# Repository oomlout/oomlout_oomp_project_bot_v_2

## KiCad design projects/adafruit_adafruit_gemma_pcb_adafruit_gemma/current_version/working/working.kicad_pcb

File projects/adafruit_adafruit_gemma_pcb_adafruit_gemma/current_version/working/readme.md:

# adafruit_gemma_pcb
 
## summary 
* id: adafruit_adafruit_gemma_pcb_adafruit_gemma
* user: adafruit
* name: adafruit_gemma_pcb
* board: adafruit_gemma
* repo: https://github.com/adafruit/Adafruit-Gemma-PCB

* src_file_repo_sch: 
* src_file_repo_sch_link: https://github.com/adafruit/Adafruit-Gemma-PCB/tree/master/
* full details link: https://github.com/oomlout/oomlout_oomp_project_bot_v_2/tree/main/projects/adafruit_adafruit_gemma_pcb_adafruit_gemma/current_version/working  

## schematic  
  
[schematic (pdf)](working_schematic.pdf) 

## pcb  

[board (pdf)](working.pdf)  

## working_bom
| Id | Designator | Footprint | Quantity | Designation | Supplier and ref |  | None | 
| --- | --- | --- | --- | --- | --- | --- | --- | 
| 1 | PWR0 | CHIPLED_0805_NOOUTLINE | 1 | green |  |  | [''] | 
| 2 | IC2 | SOT23-5L | 1 | MIC5225-3.3v |  |  | [''] | 
| 3 | C1,C8 | 0805-NO | 2 | 10uF |  |  | [''] | 
| 4 | X2 | 4UCONN_20329 | 1 | MicroUSB |  |  | [''] | 
| 5 | U$2 | ADAFRUIT_2.5MM | 1 |  |  |  | [''] | 
| 6 | VBAT0,B0,B1,B2,GND0,UNK3V3 | SEWINGTAP_2.0 | 6 | SEWTAP-2.0IN |  |  | [''] | 
| 7 | CN1 | JSTPH2 | 1 | JST-PH |  |  | [''] | 
| 8 | U1 | MLF20_4X4MM_0.5MM_ATMEL | 1 | ATTINY85 |  |  | [''] | 
| 9 | SW1 | EG1390 | 1 |  |  |  | [''] | 
| 10 | D2,D3 | SOD-123FL | 2 | SCHOTTKY |  |  | [''] | 
| 11 | R1,R2 | 0603-NO | 2 | 68 (0603) |  |  | [''] | 
| 12 | BOOT0 | CHIPLED_0805_NOOUTLINE | 1 | red |  |  | [''] | 
| 13 | R3 | 0603-NO | 1 | 1.5K (0603) |  |  | [''] | 
| 14 | Q1 | BTN_KMR2_4.6X2.8 | 1 | reset |  |  | [''] | 
| 15 | U$1,U$6 | FIDUCIAL_1MM | 2 | FIDUCIAL" |  |  | [''] | 
| 16 | R4,R5 | 0603-NO | 2 | 470 (0603) |  |  | [''] | 
| 17 | U$8 | SYMBOL_FCC_5MM | 1 |  |  |  | [''] | 
| 18 | U$10 | PCBFEAT-REV-040 | 1 |  |  |  | [''] | 
| 19 | U$7 | ADAFRUIT_5MM | 1 |  |  |  | [''] | 
| 20 | U$9 | SYMBOL_CE_5MM | 1 |  |  |  | [''] | 
| 21 | TP1 | B2,54 | 1 | TPB2,54 |  |  | [''] | 

## bom_schematic
| Ref | Qnty | Value | Cmp name | Footprint | Description | Vendor | DNP | 
| --- | --- | --- | --- | --- | --- | --- | --- | 
| B0, B1, B2 | 3 | SEWTAP-2.0IN | SEWTAP-2.0IN | working:SEWINGTAP_2.0 |  |  |  | 
| BOOT0 | 1 | red | LED0805_NOOUTLINE | working:CHIPLED_0805_NOOUTLINE |  |  |  | 
| C1, C8 | 2 | 10uF | CAP_CERAMIC0805-NOOUTLINE | working:0805-NO |  |  |  | 
| CN1 | 1 | JST-PH | CON_JST_PH_2PIN | working:JSTPH2 |  |  |  | 
| D2, D3 | 2 | SCHOTTKY | DIODE_SOD-123FL | working:SOD-123FL |  |  |  | 
| GND0 | 1 | SEWTAP-2.0IN | SEWTAP-2.0IN | working:SEWINGTAP_2.0 |  |  |  | 
| IC2 | 1 | LP298XS | LP298XS | working:SOT23-5L |  |  |  | 
| PWR0 | 1 | green | LED0805_NOOUTLINE | working:CHIPLED_0805_NOOUTLINE |  |  |  | 
| Q1 | 1 | reset | SWITCH_TACT_SMT4.6X2.8 | working:BTN_KMR2_4.6X2.8 |  |  |  | 
| R1, R2 | 2 | 68 (0603) | RESISTOR_0603_NOOUT | working:0603-NO |  |  |  | 
| R3 | 1 | 1.5K (0603) | RESISTOR_0603_NOOUT | working:0603-NO |  |  |  | 
| R4, R5 | 2 | 470 (0603) | RESISTOR_0603_NOOUT | working:0603-NO |  |  |  | 
| SW1 | 1 | SWITCH_DPDTEG1390 | SWITCH_DPDTEG1390 | working:EG1390 |  |  |  | 
| TP1 | 1 | TPB2,54 | TPB2,54 | working:B2,54 |  |  |  | 
| U1 | 1 | ATTINY85 | ATTINY85 | working:MLF20_4X4MM_0.5MM_ATMEL |  |  |  | 
| U$1, U$6 | 2 | FIDUCIAL"" | FIDUCIAL{dblquote}{dblquote} | working:FIDUCIAL_1MM |  |  |  | 
| UNK3V3 | 1 | SEWTAP-2.0IN | SEWTAP-2.0IN | working:SEWINGTAP_2.0 |  |  |  | 
| VBAT0 | 1 | SEWTAP-2.0IN | SEWTAP-2.0IN | working:SEWINGTAP_2.0 |  |  |  | 
| X2 | 1 | MicroUSB | USBMICRO_20329 | working:4UCONN_20329 |  |  |  |

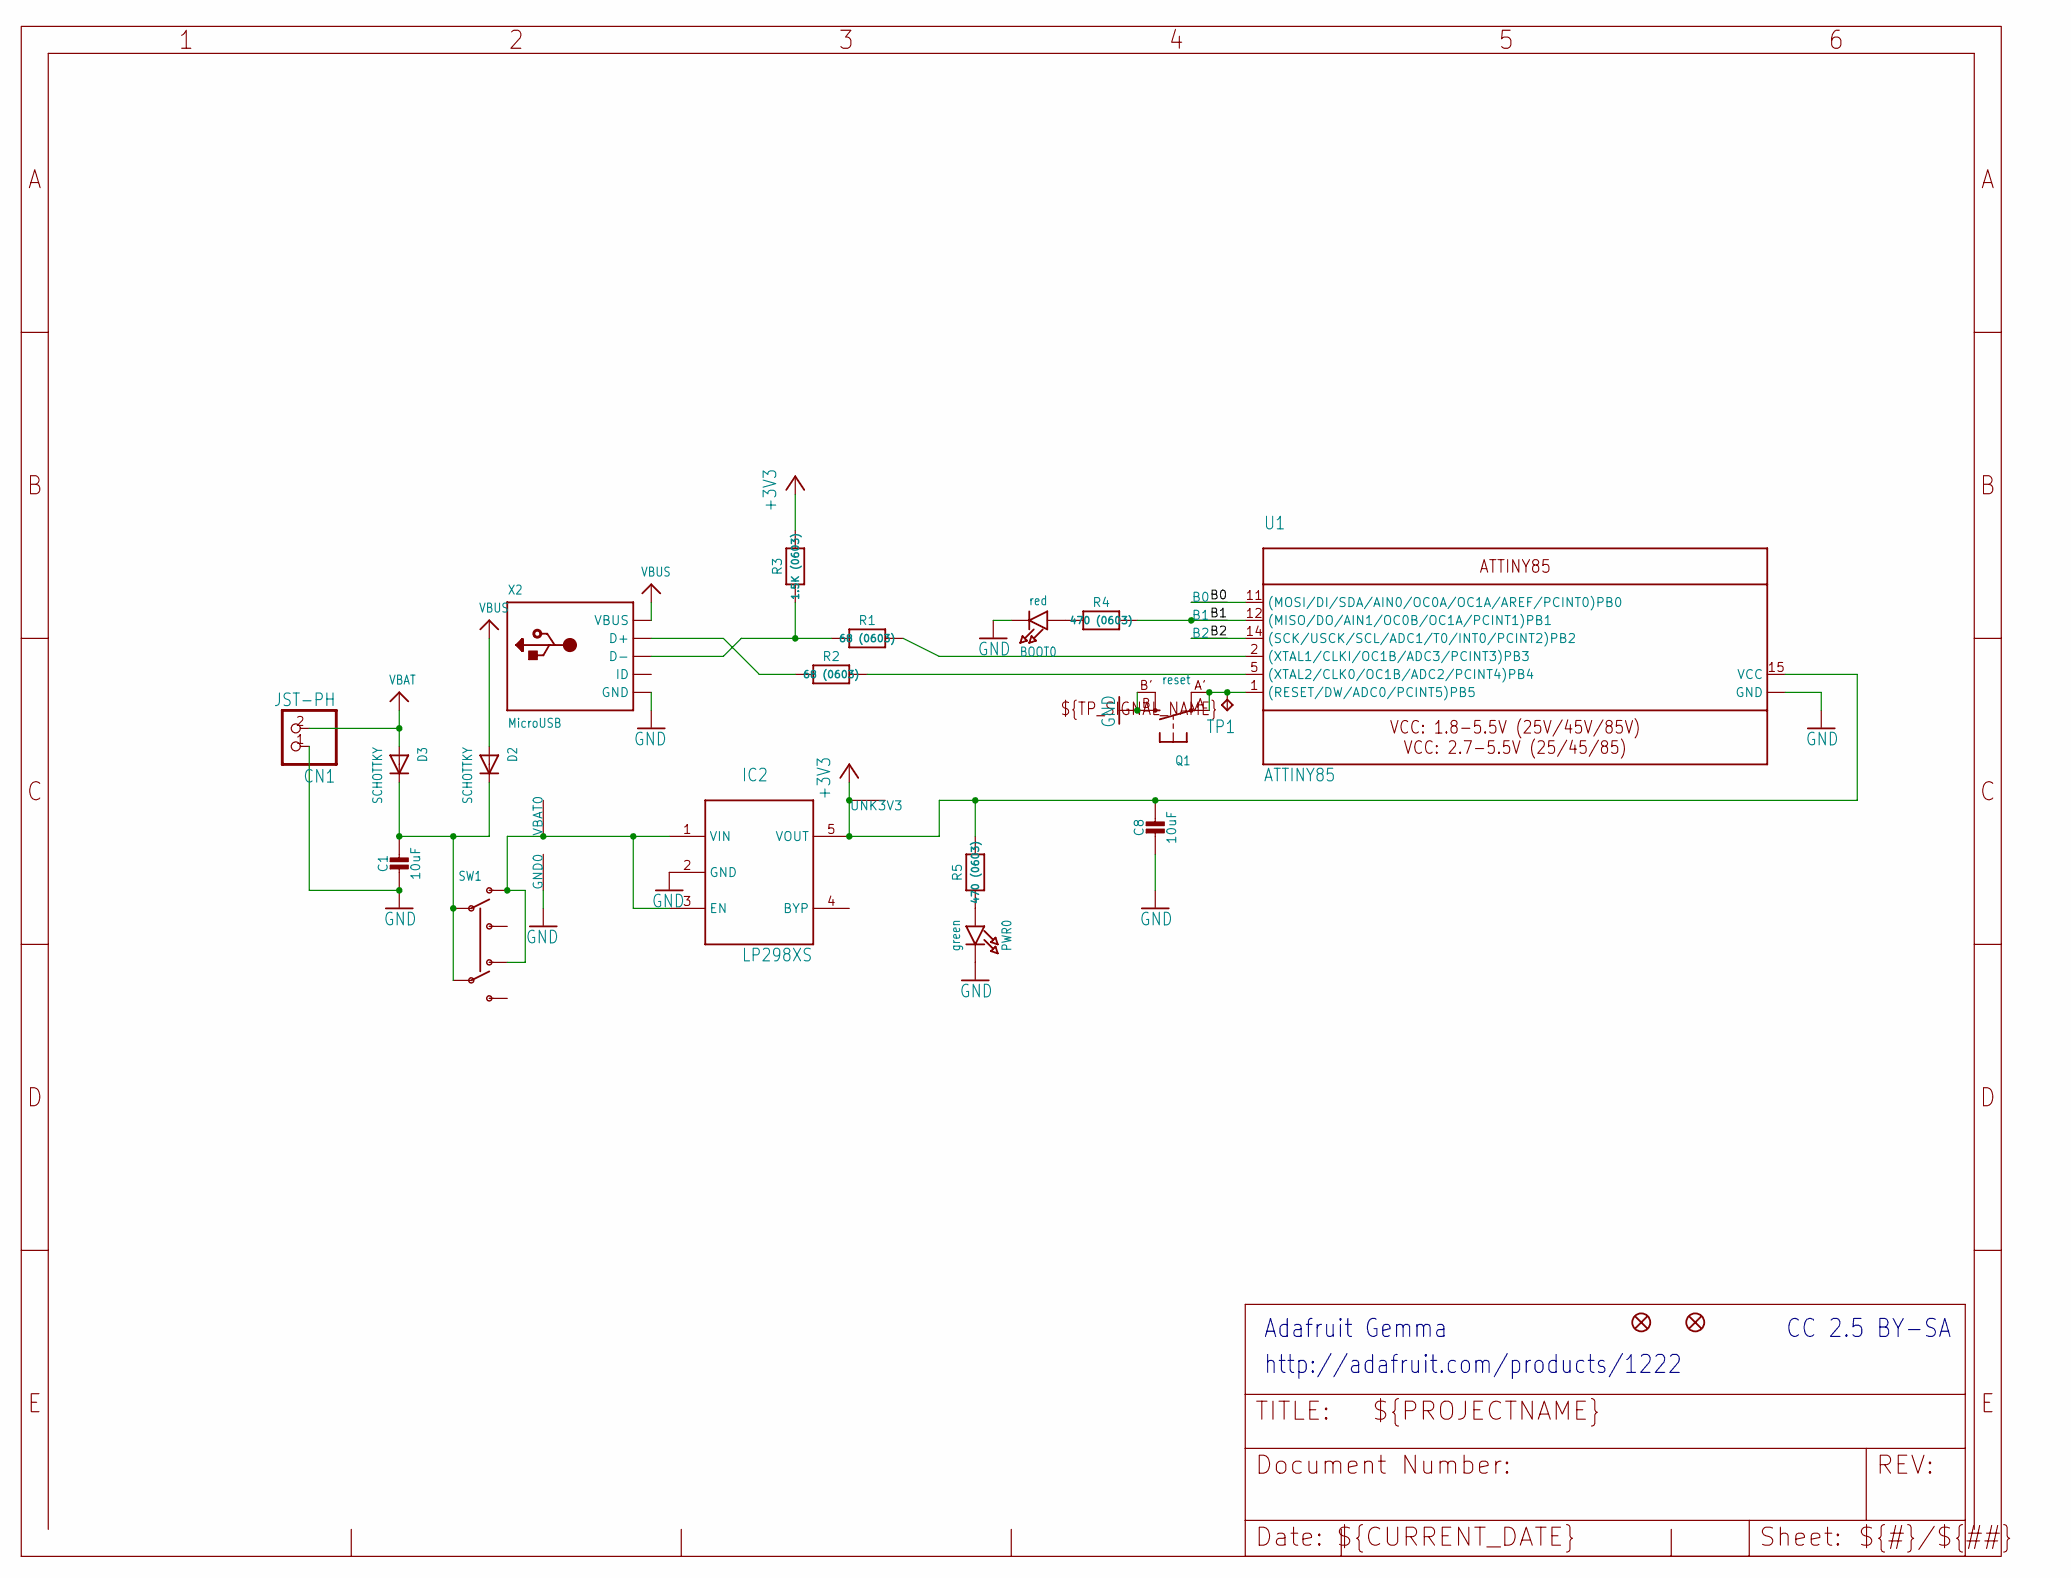
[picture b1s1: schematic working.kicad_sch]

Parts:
B0, B1, B2: SEWTAP-2.0IN; SEWINGTAP_2.0
BOOT0: red; CHIPLED_0805_NOOUTLINE
C1, C8: 10uF; 0805-NO
CN1: JST-PH; JSTPH2
D2, D3: SCHOTTKY; SOD-123FL
GND0: SEWTAP-2.0IN; SEWINGTAP_2.0
IC2: LP298XS; SOT23-5L
PWR0: green; CHIPLED_0805_NOOUTLINE
Q1: reset; BTN_KMR2_4.6X2.8
R1, R2: 68 (0603); 0603-NO
R3: 1.5K (0603); 0603-NO
R4, R5: 470 (0603); 0603-NO
SW1: SWITCH_DPDTEG1390; EG1390
TP1: TPB2,54; B2,54
U1: ATTINY85; MLF20_4X4MM_0.5MM_ATMEL
U$1, U$6: FIDUCIAL""; FIDUCIAL_1MM
UNK3V3: SEWTAP-2.0IN; SEWINGTAP_2.0
VBAT0: SEWTAP-2.0IN; SEWINGTAP_2.0
X2: MicroUSB; 4UCONN_20329

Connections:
+3V3: C8.1, IC2.5 (VOUT), R3.2, R5.2, U1.15 (VCC), UNK3V3.P$1
B0: B0.P$1, U1.11 ((MOSI/DI/SDA/AIN0/OC0A/OC1A/AREF/PCINT0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)
B1: B1.P$1, R4.2, U1.12 ((MISO/DO/AIN1/OC0B/OC1A/PCINT1)PB1)
B2: B2.P$1, U1.14 ((SCK/USCK/SCL/ADC1/T0/INT0/PCINT2)PB2)
GND: BOOT0.C, C1.2, C8.2, CN1.1, GND0.P$1, IC2.2 (GND), PWR0.C, Q1.B (S), Q1.B' (S1), U1.8 (GND), U1.THERMAL (GND), X2.BASE@1 (GND), X2.BASE@2 (GND), X2.GND, X2.SPRT@1 (GND), X2.SPRT@2 (GND), X2.SPRT@3 (GND), X2.SPRT@4 (GND)
unnamed: Q1.A, Q1.A' (P1), TP1.TP, U1.1 ((RESET/DW/ADC0/PCINT5)PB5)
unnamed: R2.1, X2.D+
unnamed: R1.2, U1.2 ((XTAL1/CLKI/OC1B/ADC3/PCINT3)PB3)
unnamed: R2.2, U1.5 ((XTAL2/CLK0/OC1B/ADC2/PCINT4)PB4)
unnamed: R1.1, R3.1, X2.D-
unnamed: BOOT0.A, R4.1
unnamed: IC2.1 (VIN), IC2.3 (EN), SW1.O1, SW1.O2, VBAT0.P$1
unnamed: PWR0.A, R5.1
unnamed: C1.1, D2.C, D3.C, SW1.P1, SW1.P2
VBAT: CN1.2, D3.A
VBUS: D2.A, X2.VBUS

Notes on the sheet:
Adafruit Gemma
http://adafruit.com/products/1222
CC 2.5 BY-SA

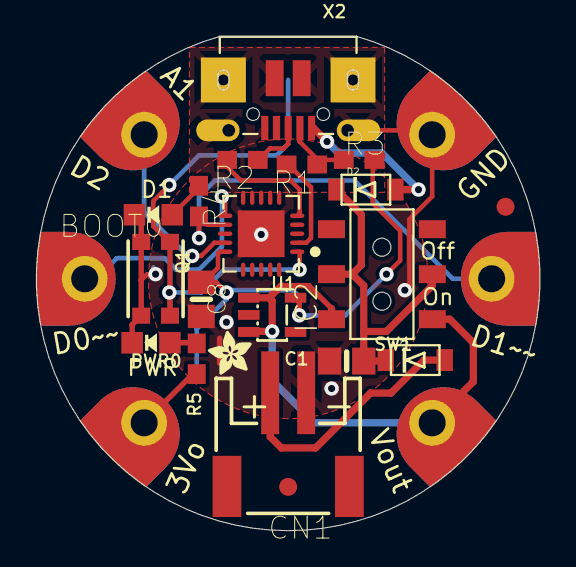
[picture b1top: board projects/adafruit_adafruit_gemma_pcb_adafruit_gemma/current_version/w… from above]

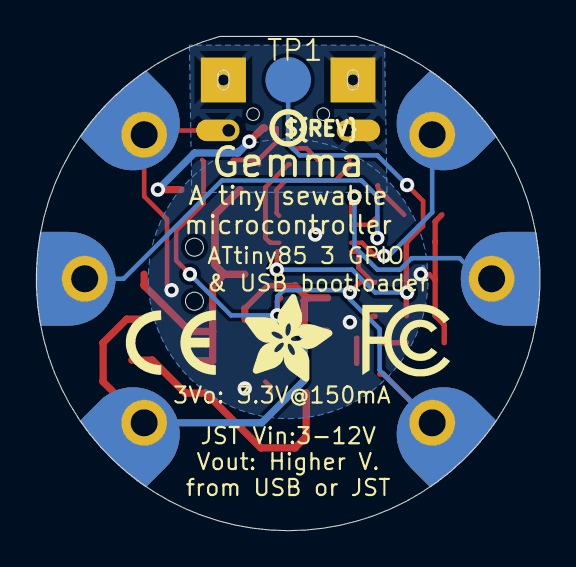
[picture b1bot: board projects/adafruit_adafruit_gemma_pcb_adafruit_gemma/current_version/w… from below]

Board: 16 copper layers, 28.0 x 27.5 mm, 31 parts (5 on the bottom side), 16 nets.

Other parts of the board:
U$2: ADAFRUIT_2.5MM
U$7: ADAFRUIT_5MM
U$8: SYMBOL_FCC_5MM
U$9: SYMBOL_CE_5MM
U$10: PCBFEAT-REV-040

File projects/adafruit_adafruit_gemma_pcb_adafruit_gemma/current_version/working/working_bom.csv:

"Id";"Designator";"Footprint";"Quantity";"Designation";"Supplier and ref";
1;"PWR0";"CHIPLED_0805_NOOUTLINE";1;"green";;;
2;"IC2";"SOT23-5L";1;"MIC5225-3.3v";;;
3;"C1,C8";"0805-NO";2;"10uF";;;
4;"X2";"4UCONN_20329";1;"MicroUSB";;;
5;"U$2";"ADAFRUIT_2.5MM";1;"";;;
6;"VBAT0,B0,B1,B2,GND0,UNK3V3";"SEWINGTAP_2.0";6;"SEWTAP-2.0IN";;;
7;"CN1";"JSTPH2";1;"JST-PH";;;
8;"U1";"MLF20_4X4MM_0.5MM_ATMEL";1;"ATTINY85";;;
9;"SW1";"EG1390";1;"";;;
10;"D2,D3";"SOD-123FL";2;"SCHOTTKY";;;
11;"R1,R2";"0603-NO";2;"68 (0603)";;;
12;"BOOT0";"CHIPLED_0805_NOOUTLINE";1;"red";;;
13;"R3";"0603-NO";1;"1.5K (0603)";;;
14;"Q1";"BTN_KMR2_4.6X2.8";1;"reset";;;
15;"U$1,U$6";"FIDUCIAL_1MM";2;"FIDUCIAL""";;;
16;"R4,R5";"0603-NO";2;"470 (0603)";;;
17;"U$8";"SYMBOL_FCC_5MM";1;"";;;
18;"U$10";"PCBFEAT-REV-040";1;"";;;
19;"U$7";"ADAFRUIT_5MM";1;"";;;
20;"U$9";"SYMBOL_CE_5MM";1;"";;;
21;"TP1";"B2,54";1;"TPB2,54";;;

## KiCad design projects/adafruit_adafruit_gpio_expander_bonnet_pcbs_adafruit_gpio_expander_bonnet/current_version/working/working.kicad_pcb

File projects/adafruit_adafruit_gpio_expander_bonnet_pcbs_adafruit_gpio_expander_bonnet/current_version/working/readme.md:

# adafruit_gpio_expander_bonnet_pcbs
 
## summary 
* id: adafruit_adafruit_gpio_expander_bonnet_pcbs_adafruit_gpio_expander_bonnet
* user: adafruit
* name: adafruit_gpio_expander_bonnet_pcbs
* board: adafruit_gpio_expander_bonnet
* repo: https://github.com/adafruit/Adafruit-GPIO-Expander-Bonnet-PCBs

* src_file_repo_sch: 
* src_file_repo_sch_link: https://github.com/adafruit/Adafruit-GPIO-Expander-Bonnet-PCBs/tree/master/
* full details link: https://github.com/oomlout/oomlout_oomp_project_bot_v_2/tree/main/projects/adafruit_adafruit_gpio_expander_bonnet_pcbs_adafruit_gpio_expander_bonnet/current_version/working  

## schematic  
  
[schematic (pdf)](working_schematic.pdf) 

## pcb  

[board (pdf)](working.pdf)  

## working_bom
| Id | Designator | Footprint | Quantity | Designation | Supplier and ref |  | None | 
| --- | --- | --- | --- | --- | --- | --- | --- | 
| 1 | IC1 | QFN28-ML_6X6MM | 1 | MCP23017ML |  |  | [''] | 
| 2 | U1 | SOT23-5 | 1 |  |  |  | [''] | 
| 3 | U$13 | PCBFEAT-REV-040 | 1 |  |  |  | [''] | 
| 4 | ADDR2,ADDR1,ADDR0 | SOLDERJUMPER_ARROW_NOPASTE | 3 |  |  |  | [''] | 
| 5 | R2,R3,R8,R9,R1,R4,R5,R6,R7 | 0603-NO | 9 | 10K |  |  | [''] | 
| 6 | Q2,Q1 | SOT23-WIDE | 2 | BSS138 |  |  | [''] | 
| 7 | FID1,FID2 | FIDUCIAL_1MM | 2 | FIDUCIAL_1MM |  |  | [''] | 
| 8 | JP8,JP3,JP5,JP6,JP9,JP1 | 1X02_ROUND | 6 |  |  |  | [''] | 
| 9 | RPI2 | PI_BONNET_2STEMMA_SMT | 1 | PIBONNET_STEMMA_2STEMMA_SMTTHM |  |  | [''] | 
| 10 | U$12 | ADAFRUIT_5MM | 1 |  |  |  | [''] | 
| 11 | JP2,JP7 | 2X08_SHROUDED | 2 |  |  |  | [''] | 
| 12 | C2 | 0603-NO | 1 | 0.1uF |  |  | [''] | 
| 13 | VIO_SELECT0 | SOLDERJUMPER_2WAY_OPEN_NOPASTE | 1 |  |  |  | [''] | 
| 14 | PIN1 | 1X21_ROUND_70MIL | 1 | HEADER-1X21 |  |  | [''] | 
| 15 | C3,C1 | 0805-NO | 2 | 10uF |  |  | [''] | 

## bom_schematic
| Ref | Qnty | Value | Cmp name | Footprint | Description | Vendor | DNP | 
| --- | --- | --- | --- | --- | --- | --- | --- | 
| ADDR0, ADDR1, ADDR2 | 3 | SOLDERJUMPER | SOLDERJUMPER | working:SOLDERJUMPER_ARROW_NOPASTE |  |  |  | 
| C1, C3 | 2 | 10uF | CAP_CERAMIC0805-NOOUTLINE | working:0805-NO |  |  |  | 
| C2 | 1 | 0.1uF | CAP_CERAMIC0603_NO | working:0603-NO |  |  |  | 
| FID1, FID2 | 2 | FIDUCIAL_1MM | FIDUCIAL_1MM | working:FIDUCIAL_1MM |  |  |  | 
| IC1 | 1 | MCP23017ML | MCP23017ML | working:QFN28-ML_6X6MM |  |  |  | 
| JP1, JP3, JP5, JP6, JP8, JP9 | 6 | HEADER-1X2ROUND | HEADER-1X2ROUND | working:1X02_ROUND |  |  |  | 
| JP2, JP7 | 2 | HEADER-2X8_SHROUDED | HEADER-2X8_SHROUDED | working:2X08_SHROUDED |  |  |  | 
| PIN1 | 1 | HEADER-1X21 | HEADER-1X21 | working:1X21_ROUND_70MIL |  |  |  | 
| Q1, Q2 | 2 | BSS138 | MOSFET-NWIDE | working:SOT23-WIDE |  |  |  | 
| R1, R2, R3, R4, R5, R6, R7, R8, R9 | 9 | 10K | RESISTOR_0603_NOOUT | working:0603-NO |  |  |  | 
| RPI2 | 1 | PIBONNET_STEMMA_2STEMMA_SMTTHM | PIBONNET_STEMMA_2STEMMA_SMTTHM | working:PI_BONNET_2STEMMA_SMT |  |  |  | 
| U1 | 1 | VREG_SOT23-5 | VREG_SOT23-5 | working:SOT23-5 |  |  |  | 
| VIO_SELECT0 | 1 | SOLDERJUMPER_2WAY | SOLDERJUMPER_2WAY | working:SOLDERJUMPER_2WAY_OPEN_NOPASTE |  |  |  |

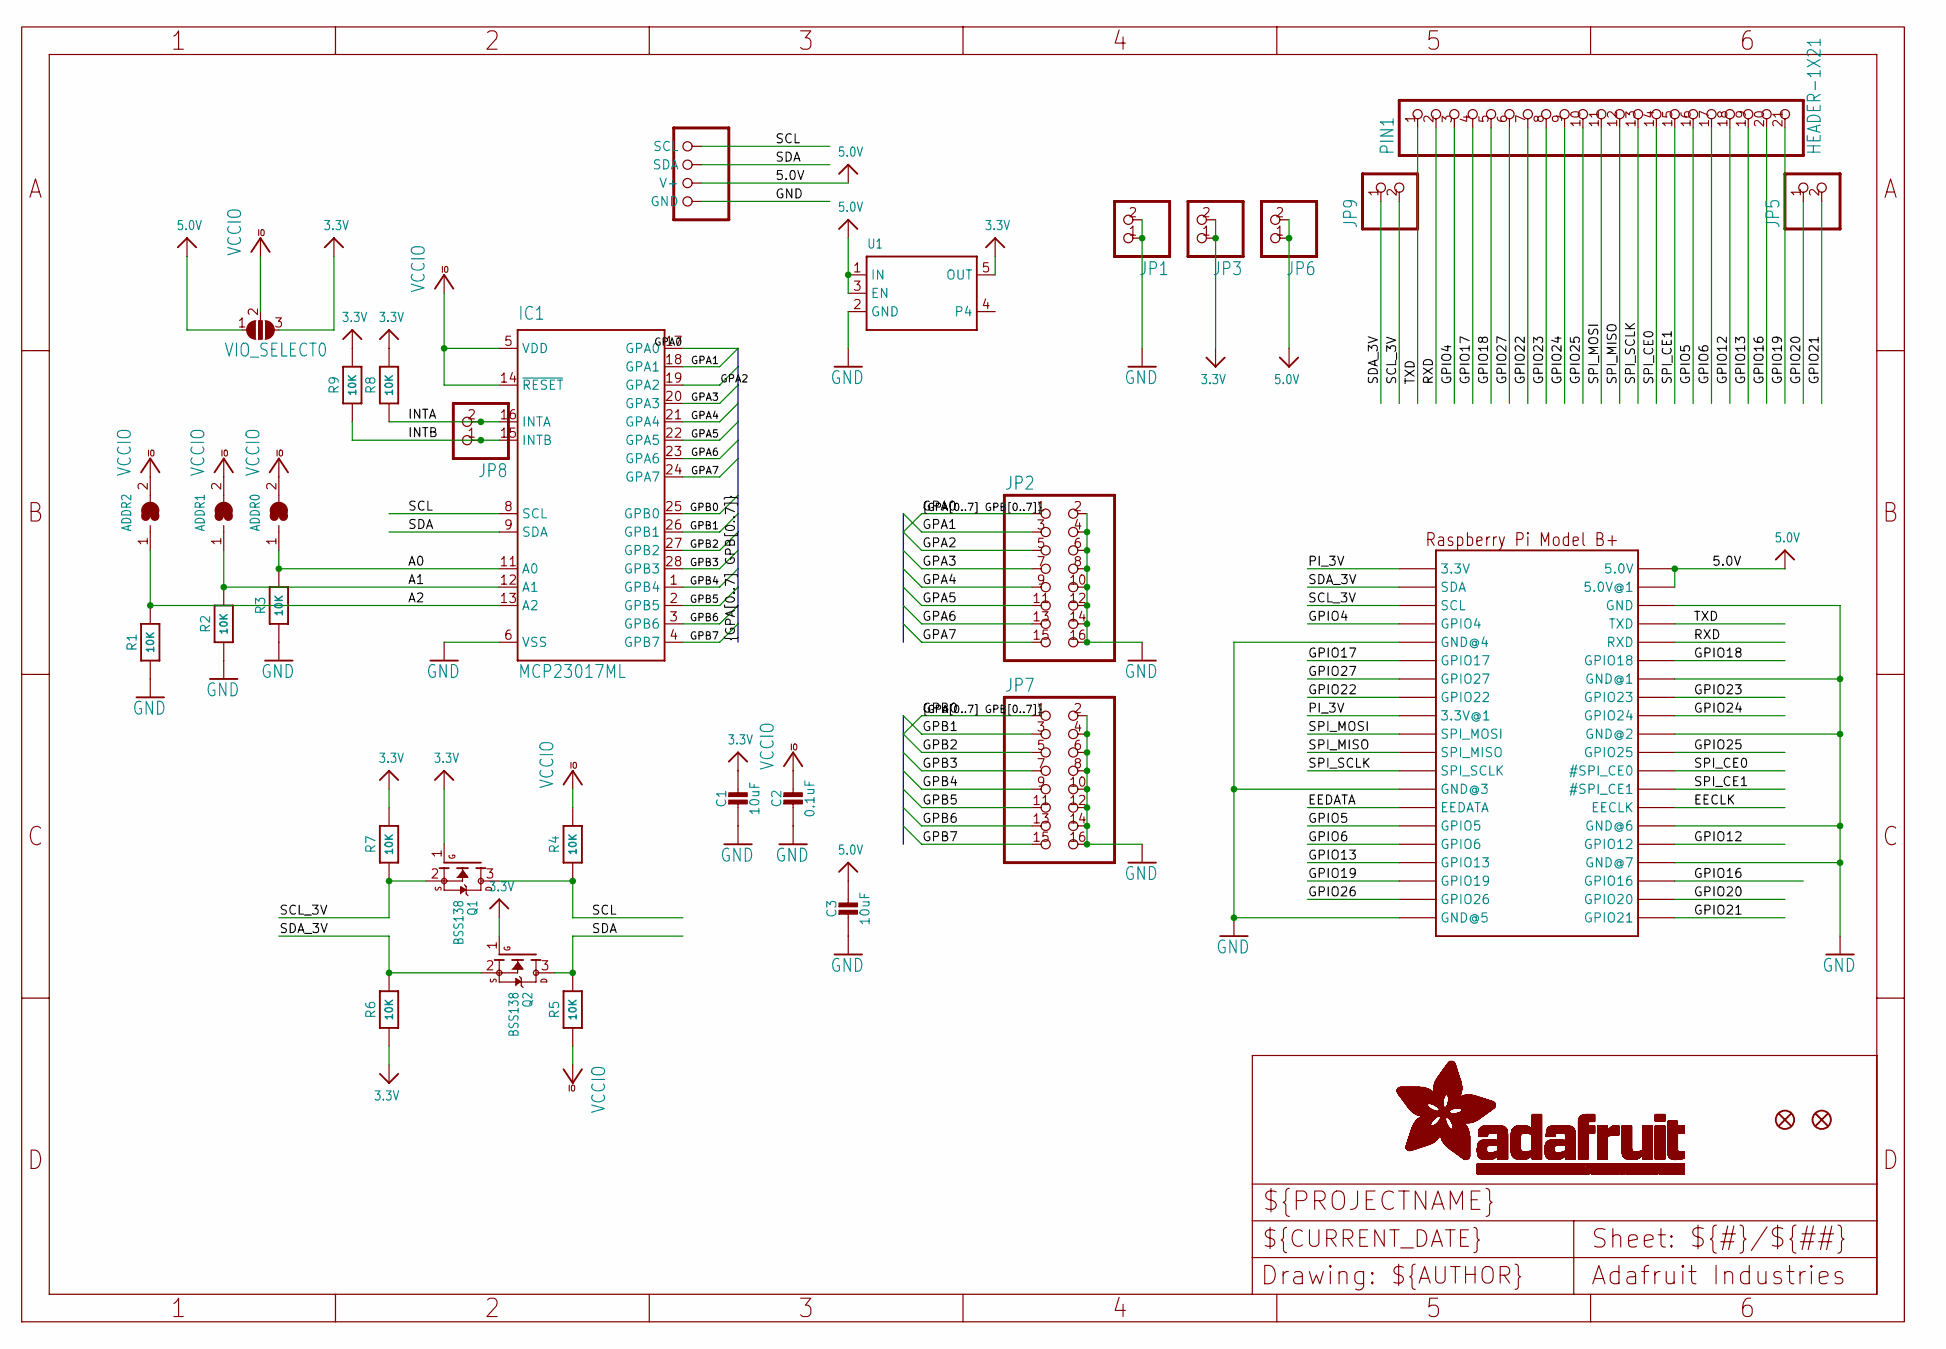
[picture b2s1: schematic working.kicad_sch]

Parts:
ADDR0, ADDR1, ADDR2: SOLDERJUMPER; SOLDERJUMPER_ARROW_NOPASTE
C1, C3: 10uF; 0805-NO
C2: 0.1uF; 0603-NO
FID1, FID2: FIDUCIAL_1MM
IC1: MCP23017ML; QFN28-ML_6X6MM
JP1, JP3, JP5, JP6, JP8, JP9: HEADER-1X2ROUND; 1X02_ROUND
JP2, JP7: HEADER-2X8_SHROUDED; 2X08_SHROUDED
PIN1: HEADER-1X21; 1X21_ROUND_70MIL
Q1, Q2: BSS138; SOT23-WIDE
R1, R2, R3, R4, R5, R6, R7, R8, R9: 10K; 0603-NO
RPI2: PIBONNET_STEMMA_2STEMMA_SMTTHM; PI_BONNET_2STEMMA_SMT
U1: VREG_SOT23-5; SOT23-5
VIO_SELECT0: SOLDERJUMPER_2WAY; SOLDERJUMPER_2WAY_OPEN_NOPASTE

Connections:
3.3V: C1.1, JP3.1, JP3.2, Q1.1 (G), Q2.1 (G), R6.1, R7.2, R8.2, R9.2, U1.5 (OUT), VIO_SELECT0.3
5.0V: C3.1, JP6.1, JP6.2, RPI2.2 (5.0V), RPI2.4 (5.0V@1), RPI2.S2 (5.0V), RPI2.S4 (5.0V@1), RPI2.V+, RPI2.V+1 (V+), U1.1 (IN), U1.3 (EN), VIO_SELECT0.1
A0: ADDR0.1, IC1.11 (A0), R3.2
A1: ADDR1.1, IC1.12 (A1), R2.2
A2: ADDR2.1, IC1.13 (A2), R1.2
EECLK: RPI2.28 (EECLK), RPI2.S28 (EECLK)
EEDATA: RPI2.27 (EEDATA), RPI2.S27 (EEDATA)
GND: C1.2, C2.2, C3.2, IC1.6 (VSS), JP1.1, JP1.2, JP2.2, JP2.4, JP2.6, JP2.8, JP2.10, JP2.12, JP2.14, JP2.16, JP7.2, JP7.4, JP7.6, JP7.8, JP7.10, JP7.12, JP7.14, JP7.16, R1.1, R2.1, R3.1, RPI2.6 (GND), RPI2.9 (GND@4), RPI2.14 (GND@1), RPI2.20 (GND@2), RPI2.25 (GND@3), RPI2.30 (GND@6), RPI2.34 (GND@7), RPI2.39 (GND@5), RPI2.GND, RPI2.GND1 (GND), RPI2.S6 (GND), RPI2.S9 (GND@4), RPI2.S14 (GND@1), RPI2.S20 (GND@2), RPI2.S25 (GND@3), RPI2.S30 (GND@6), RPI2.S34 (GND@7), RPI2.S39 (GND@5), U1.2 (GND)
GPA1: IC1.18 (GPA1), JP2.3
GPA2: IC1.19 (GPA2), JP2.5
GPA3: IC1.20 (GPA3), JP2.7
GPA4: IC1.21 (GPA4), JP2.9
GPA5: IC1.22 (GPA5), JP2.11
GPA6: IC1.23 (GPA6), JP2.13
GPA7: IC1.24 (GPA7), JP2.15
GPB1: IC1.26 (GPB1), JP7.3
GPB2: IC1.27 (GPB2), JP7.5
GPB3: IC1.28 (GPB3), JP7.7
GPB4: IC1.1 (GPB4), JP7.9
GPB5: IC1.2 (GPB5), JP7.11
GPB6: IC1.3 (GPB6), JP7.13
GPB7: IC1.4 (GPB7), JP7.15
GPIO4: PIN1.3, RPI2.7 (GPIO4), RPI2.S7 (GPIO4)
GPIO5: PIN1.16, RPI2.29 (GPIO5), RPI2.S29 (GPIO5)
GPIO6: PIN1.17, RPI2.31 (GPIO6), RPI2.S31 (GPIO6)
GPIO12: PIN1.18, RPI2.32 (GPIO12), RPI2.S32 (GPIO12)
GPIO13: PIN1.19, RPI2.33 (GPIO13), RPI2.S33 (GPIO13)
GPIO16: PIN1.20, RPI2.36 (GPIO16), RPI2.S36 (GPIO16)
GPIO17: PIN1.4, RPI2.11 (GPIO17), RPI2.S11 (GPIO17)
GPIO18: PIN1.5, RPI2.12 (GPIO18), RPI2.S12 (GPIO18)
GPIO19: PIN1.21, RPI2.35 (GPIO19), RPI2.S35 (GPIO19)
GPIO20: JP5.1, RPI2.38 (GPIO20), RPI2.S38 (GPIO20)
GPIO21: JP5.2, RPI2.40 (GPIO21), RPI2.S40 (GPIO21)
GPIO22: PIN1.7, RPI2.15 (GPIO22), RPI2.S15 (GPIO22)
GPIO23: PIN1.8, RPI2.16 (GPIO23), RPI2.S16 (GPIO23)
GPIO24: PIN1.9, RPI2.18 (GPIO24), RPI2.S18 (GPIO24)
GPIO25: PIN1.10, RPI2.22 (GPIO25), RPI2.S22 (GPIO25)
GPIO26: RPI2.37 (GPIO26), RPI2.S37 (GPIO26)
GPIO27: PIN1.6, RPI2.13 (GPIO27), RPI2.S13 (GPIO27)
INTA: IC1.16 (INTA), JP8.2, R8.1
INTB: IC1.15 (INTB), JP8.1, R9.1
PI_3V: RPI2.1 (3.3V), RPI2.17 (3.3V@1), RPI2.S1 (3.3V), RPI2.S17 (3.3V@1)
RXD: PIN1.2, RPI2.10 (RXD), RPI2.S10 (RXD)
SCL: IC1.8 (SCL), Q1.3 (D), R4.1, RPI2.SCL, RPI2.SCL1 (SCL)
SCL_3V: JP9.2, Q1.2 (S), R7.1, RPI2.5 (SCL), RPI2.S5 (SCL)
SDA: IC1.9 (SDA), Q2.3 (D), R5.2, RPI2.SDA, RPI2.SDA1 (SDA)
SDA_3V: JP9.1, Q2.2 (S), R6.2, RPI2.3 (SDA), RPI2.S3 (SDA)
SPI_CE0: PIN1.14, RPI2.24 (#SPI_CE0), RPI2.S24 (#SPI_CE0)
SPI_CE1: PIN1.15, RPI2.26 (#SPI_CE1), RPI2.S26 (#SPI_CE1)
SPI_MISO: PIN1.12, RPI2.21 (SPI_MISO), RPI2.S21 (SPI_MISO)
SPI_MOSI: PIN1.11, RPI2.19 (SPI_MOSI), RPI2.S19 (SPI_MOSI)
SPI_SCLK: PIN1.13, RPI2.23 (SPI_SCLK), RPI2.S23 (SPI_SCLK)
TXD: PIN1.1, RPI2.8 (TXD), RPI2.S8 (TXD)
VCCIO: ADDR0.2, ADDR1.2, ADDR2.2, C2.1, IC1.5 (VDD), IC1.14 (~RESET), R4.2, R5.1, VIO_SELECT0.2

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
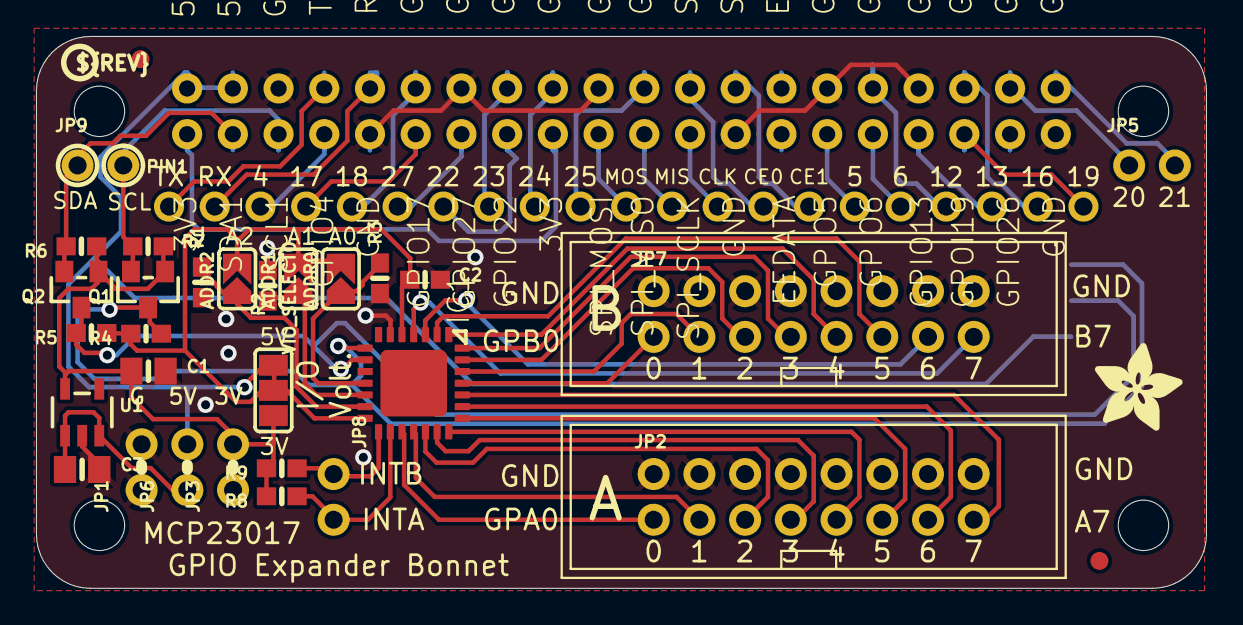
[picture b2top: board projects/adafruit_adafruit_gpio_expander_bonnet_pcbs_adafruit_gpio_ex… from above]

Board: 2 copper layers, 65.0 x 30.7 mm, 34 parts (0 on the bottom side), 56 nets.

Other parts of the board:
U$12: ADAFRUIT_5MM
U$13: PCBFEAT-REV-040

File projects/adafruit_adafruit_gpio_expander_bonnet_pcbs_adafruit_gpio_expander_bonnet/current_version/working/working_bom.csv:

"Id";"Designator";"Footprint";"Quantity";"Designation";"Supplier and ref";
1;"IC1";"QFN28-ML_6X6MM";1;"MCP23017ML";;;
2;"U1";"SOT23-5";1;"";;;
3;"U$13";"PCBFEAT-REV-040";1;"";;;
4;"ADDR2,ADDR1,ADDR0";"SOLDERJUMPER_ARROW_NOPASTE";3;"";;;
5;"R2,R3,R8,R9,R1,R4,R5,R6,R7";"0603-NO";9;"10K";;;
6;"Q2,Q1";"SOT23-WIDE";2;"BSS138";;;
7;"FID1,FID2";"FIDUCIAL_1MM";2;"FIDUCIAL_1MM";;;
8;"JP8,JP3,JP5,JP6,JP9,JP1";"1X02_ROUND";6;"";;;
9;"RPI2";"PI_BONNET_2STEMMA_SMT";1;"PIBONNET_STEMMA_2STEMMA_SMTTHM";;;
10;"U$12";"ADAFRUIT_5MM";1;"";;;
11;"JP2,JP7";"2X08_SHROUDED";2;"";;;
12;"C2";"0603-NO";1;"0.1uF";;;
13;"VIO_SELECT0";"SOLDERJUMPER_2WAY_OPEN_NOPASTE";1;"";;;
14;"PIN1";"1X21_ROUND_70MIL";1;"HEADER-1X21";;;
15;"C3,C1";"0805-NO";2;"10uF";;;

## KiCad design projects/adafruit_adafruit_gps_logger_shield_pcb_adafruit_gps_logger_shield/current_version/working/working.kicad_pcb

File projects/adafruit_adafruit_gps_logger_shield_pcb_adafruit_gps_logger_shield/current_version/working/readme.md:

# adafruit_gps_logger_shield_pcb
 
## summary 
* id: adafruit_adafruit_gps_logger_shield_pcb_adafruit_gps_logger_shield
* user: adafruit
* name: adafruit_gps_logger_shield_pcb
* board: adafruit_gps_logger_shield
* repo: https://github.com/adafruit/Adafruit-GPS-Logger-Shield-PCB

* src_file_repo_sch: 
* src_file_repo_sch_link: https://github.com/adafruit/Adafruit-GPS-Logger-Shield-PCB/tree/master/
* full details link: https://github.com/oomlout/oomlout_oomp_project_bot_v_2/tree/main/projects/adafruit_adafruit_gps_logger_shield_pcb_adafruit_gps_logger_shield/current_version/working  

## schematic  
  
[schematic (pdf)](working_schematic.pdf) 

## pcb  

[board (pdf)](working.pdf)  

## working_bom
| Id | Designator | Footprint | Quantity | Designation | Supplier and ref |  | None | 
| --- | --- | --- | --- | --- | --- | --- | --- | 
| 1 | FB1 | 0805@1 | 1 | Ferrite |  |  | [''] | 
| 2 | @HOLE0,@HOLE2,@HOLE1 |  | 3 |  |  |  | [''] | 
| 3 | C2,C3 | 0805@1 | 2 | 10uF |  |  | [''] | 
| 4 | U1 | FGPMMOPA6H | 1 | FGPMMOPA6H |  |  | [''] | 
| 5 | FID2,FID1 | FIDUCIAL_1MM | 2 | FIDUCIAL" |  |  | [''] | 
| 6 | JP9,JP6 | 1X06-BIG | 2 |  |  |  | [''] | 
| 7 | U$9 | 1X10-BIG | 1 | PINHD-1X10 |  |  | [''] | 
| 8 | RESET0 | EVQ-Q2 | 1 | Reset |  |  | [''] | 
| 9 | R9,R10 | 0805 | 2 | 1k |  |  | [''] | 
| 10 | U$13 | ADAFRUIT_5MM | 1 |  |  |  | [''] | 
| 11 | R5 | 0805 | 1 | 10K |  |  | [''] | 
| 12 | C1 | 0805@1 | 1 | 0.1uF |  |  | [''] | 
| 13 | LED5 | CHIPLED_0805 | 1 | green |  |  | [''] | 
| 14 | U4 | SOIC16 | 1 | 4050 |  |  | [''] | 
| 15 | U2 | SOT23-5 | 1 | MIC5225-3.3 |  |  | [''] | 
| 16 | JP4,JP1 | 1X08-BIG | 2 | D0-D7 |  |  | [''] | 
| 17 | R1 | 0805 | 1 | 1K |  |  | [''] | 
| 18 | B1 | CR1220 | 1 | CR1220 |  |  | [''] | 
| 19 | SW1 | EG1390 | 1 |  |  |  | [''] | 
| 20 | U$20 | U.FL | 1 | U.FL |  |  | [''] | 
| 21 | CN2 | MICROSD | 1 |  |  |  | [''] | 
| 22 | LED4 | CHIPLED_0805 | 1 | yellow |  |  | [''] | 
| 23 | U3 | ARDUINOR3 | 1 | ARDUINOR3-DIMENSION |  |  | [''] | 
| 24 | LED1 | CHIPLED_0805 | 1 | red |  |  | [''] | 
| 25 | U$15 | ADAFRUIT_TEXT_30MM | 1 |  |  |  | [''] | 

## bom_schematic
| Ref | Qnty | Value | Cmp name | Footprint | Description | Vendor | DNP | 
| --- | --- | --- | --- | --- | --- | --- | --- | 
| B1 | 1 | CR1220 | BATTERYCR1220_SMT | working:CR1220 |  |  |  | 
| C1 | 1 | 0.1uF | CAP_CERAMIC0805 | working:0805@1 |  |  |  | 
| C2, C3 | 2 | 10uF | CAP_CERAMIC0805 | working:0805@1 |  |  |  | 
| CN2 | 1 | MICROSD | MICROSD | working:MICROSD |  |  |  | 
| FB1 | 1 | Ferrite | FERRITE0805 | working:0805@1 |  |  |  | 
| FID1, FID2 | 2 | FIDUCIAL"" | FIDUCIAL{dblquote}{dblquote} | working:FIDUCIAL_1MM |  |  |  | 
| JP1, JP4 | 2 | D0-D7 | PINHD-1X8BIG | working:1X08-BIG |  |  |  | 
| JP6, JP9 | 2 | PINHD-1X6B | PINHD-1X6B | working:1X06-BIG |  |  |  | 
| LED1 | 1 | red | LED0805 | working:CHIPLED_0805 |  |  |  | 
| LED4 | 1 | yellow | LED0805 | working:CHIPLED_0805 |  |  |  | 
| LED5 | 1 | green | LED0805 | working:CHIPLED_0805 |  |  |  | 
| R1 | 1 | 1K | RESISTOR0805 | working:0805 |  |  |  | 
| R5 | 1 | 10K | RESISTOR0805 | working:0805 |  |  |  | 
| R9, R10 | 2 | 1k | RESISTOR0805 | working:0805 |  |  |  | 
| RESET0 | 1 | SPST_TACT-EVQQ2 | SPST_TACT-EVQQ2 | working:EVQ-Q2 |  |  |  | 
| SW1 | 1 | DPDT-EG1390 | DPDT-EG1390 | working:EG1390 |  |  |  | 
| U1 | 1 | FGPMMOPA6H | GPS_FGPMMOPA6H | working:FGPMMOPA6H |  |  |  | 
| U2 | 1 | MIC5225-3.3 | VREG_SOT23-5 | working:SOT23-5 |  |  |  | 
| U3 | 1 | ARDUINOR3-DIMENSION | ARDUINOR3-DIMENSION | working:ARDUINOR3 |  |  |  | 
| U4 | 1 | 4050 | 74HC4050D | working:SOIC16 |  |  |  | 
| U$9 | 1 | PINHD-1X10 | PINHD-1X10 | working:1X10-BIG |  |  |  | 
| U$20 | 1 | U.FL | U.FL | working:U.FL |  |  |  |

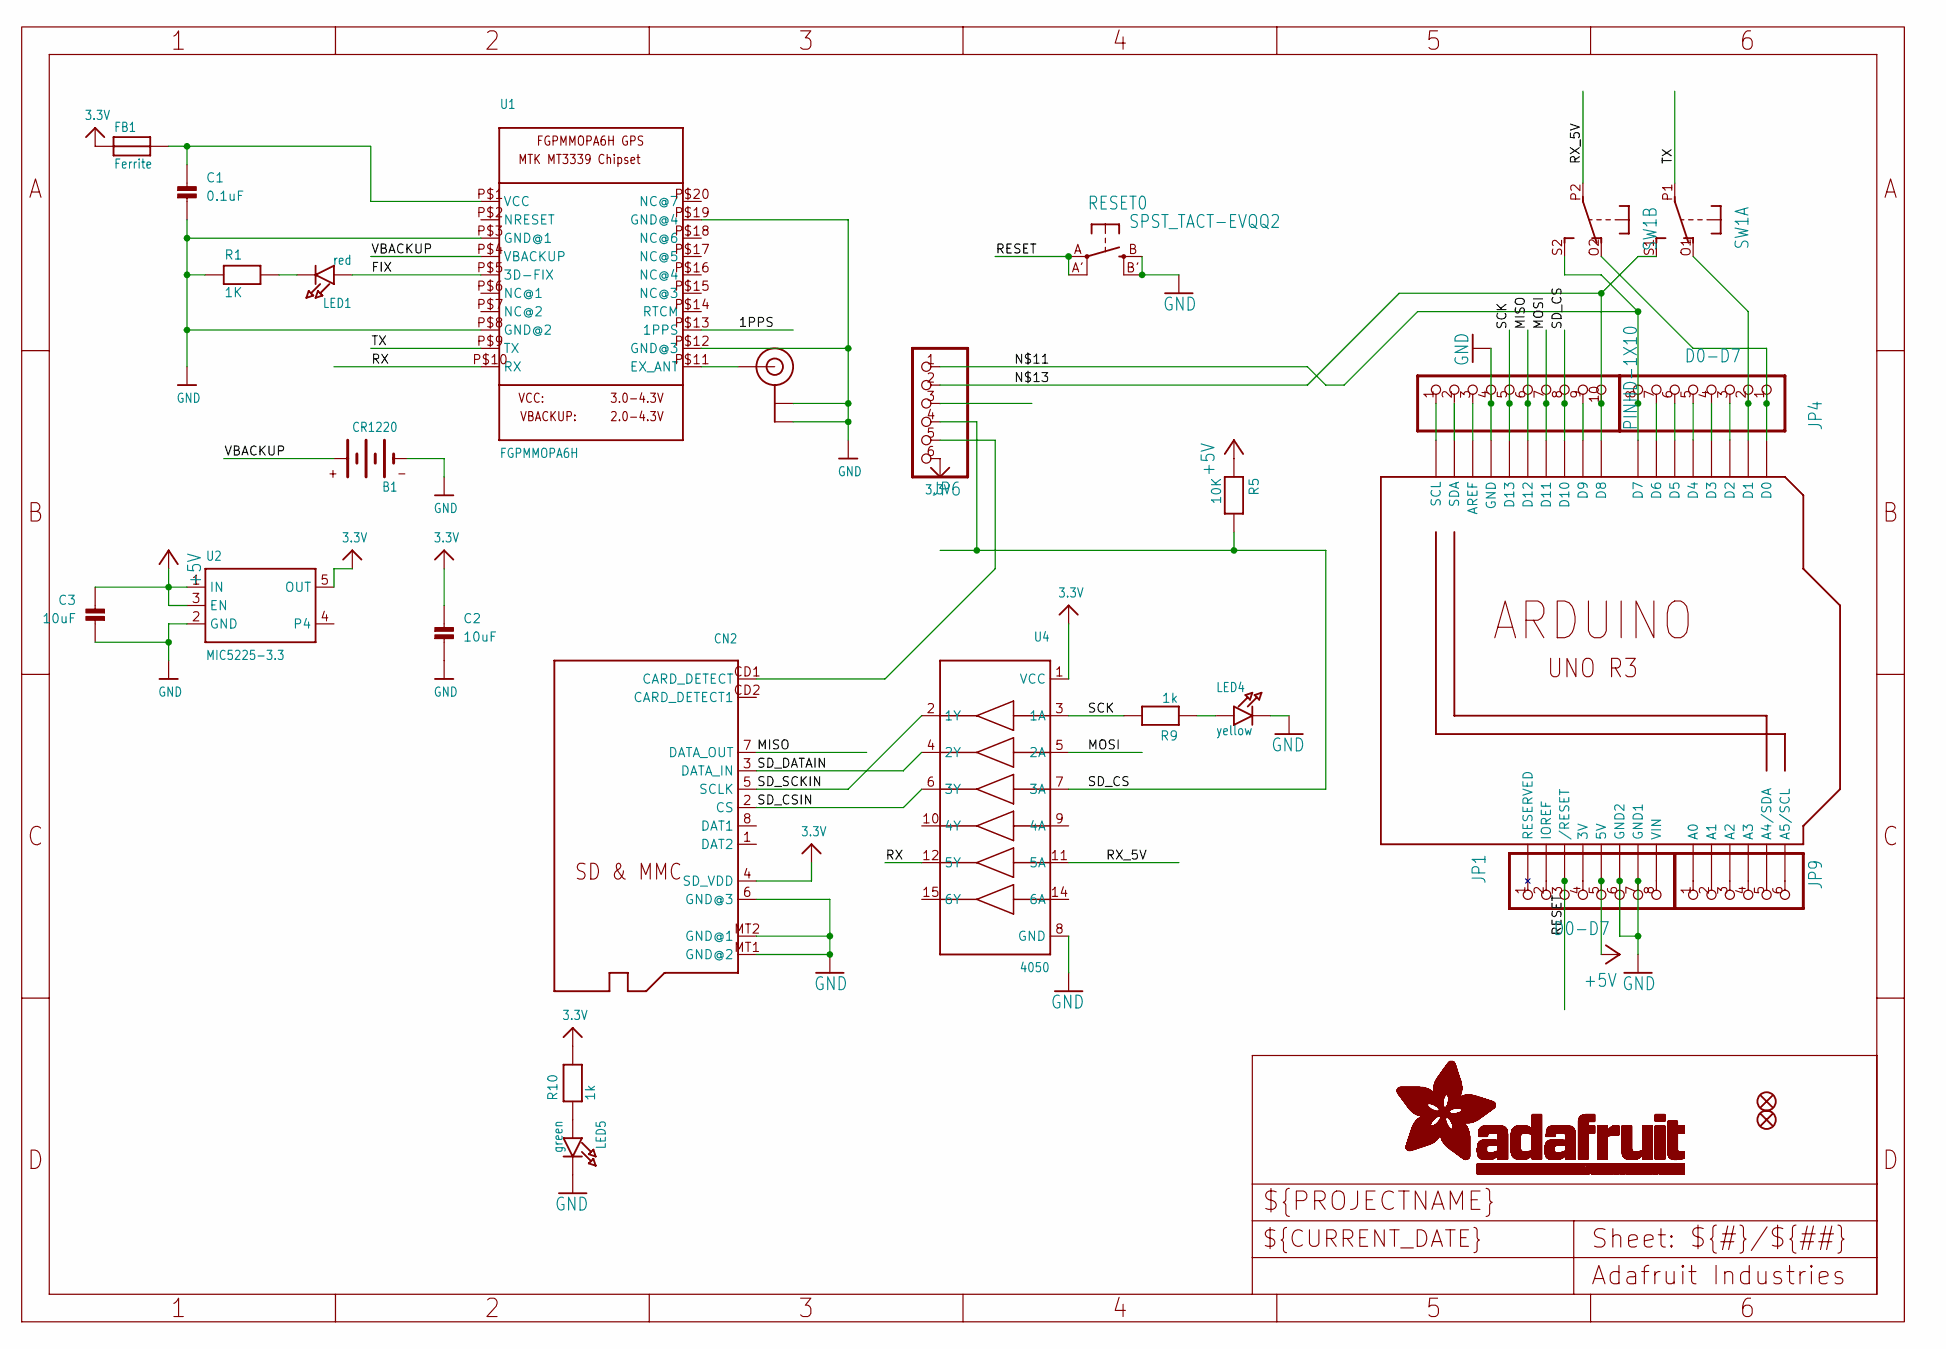
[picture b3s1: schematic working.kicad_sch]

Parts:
B1: CR1220
C1: 0.1uF; 0805@1
C2, C3: 10uF; 0805@1
CN2: MICROSD
FB1: Ferrite; 0805@1
FID1, FID2: FIDUCIAL""; FIDUCIAL_1MM
JP1, JP4: D0-D7; 1X08-BIG
JP6, JP9: PINHD-1X6B; 1X06-BIG
LED1: red; CHIPLED_0805
LED4: yellow; CHIPLED_0805
LED5: green; CHIPLED_0805
R1: 1K; 0805
R5: 10K; 0805
R9, R10: 1k; 0805
RESET0: SPST_TACT-EVQQ2; EVQ-Q2
SW1: DPDT-EG1390; EG1390
U1: FGPMMOPA6H
U2: MIC5225-3.3; SOT23-5
U3: ARDUINOR3-DIMENSION; ARDUINOR3
U4: 4050; SOIC16
U$9: PINHD-1X10; 1X10-BIG
U$20: U.FL

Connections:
1PPS: JP6.3, U1.P$13 (1PPS)
3.3V: C2.1, CN2.4 (SD_VDD), FB1.1, JP6.6, R10.2, U2.5 (OUT), U4.1 (VCC)
+5V: C3.1, JP1.5, R5.1, U2.1 (IN), U2.3 (EN), U3.5V
FIX: LED1.A, U1.P$5 (3D-FIX)
GND: B1.-, C1.2, C2.2, C3.2, CN2.6 (GND@3), CN2.MT1 (GND@2), CN2.MT2 (GND@1), JP1.6, JP1.7, LED4.C, LED5.C, R1.1, RESET0.B (S), RESET0.B' (S1), U1.P$3 (GND@1), U1.P$8 (GND@2), U1.P$12 (GND@3), U1.P$19 (GND@4), U2.2 (GND), U3.GND, U3.GND1, U3.GND2, U4.8 (GND), U$9.4, U$20.P$1 (GND@0), U$20.P$2 (GND@1)
MISO: CN2.7 (DATA_OUT), U3.D12, U$9.6
MOSI: U3.D11, U4.5 (2A), U$9.7
unnamed: C1.1, FB1.2, U1.P$1 (VCC)
unnamed: LED1.C, R1.2
unnamed: JP1.1, U3.RESERVED
unnamed: U1.P$11 (EX_ANT), U$20.P$3 (SIGNAL)
unnamed: JP1.2, U3.IOREF
unnamed: JP1.4, U3.3V
unnamed: U3.SCL, U$9.1
unnamed: LED4.A, R9.1
unnamed: JP9.6, U3.A5 (A5/SCL)
unnamed: JP9.5, U3.A4 (A4/SDA)
unnamed: JP4.8, JP6.1, SW1.S2 (S), U3.D7
unnamed: U3.SDA, U$9.2
unnamed: JP6.2, SW1.S1 (S), U3.D8, U$9.10
unnamed: JP4.2, SW1.O1 (O), U3.D1
unnamed: JP1.8, U3.VIN
unnamed: JP4.3, U3.D2
unnamed: JP4.4, U3.D3
unnamed: JP4.5, U3.D4
unnamed: JP4.6, U3.D5
unnamed: JP4.7, U3.D6
unnamed: U3.AREF, U$9.3
unnamed: U3.D9, U$9.9
unnamed: LED5.A, R10.1
unnamed: JP9.1, U3.A0
unnamed: JP9.2, U3.A1
unnamed: JP9.3, U3.A2
unnamed: JP9.4, U3.A3
unnamed: JP4.1, SW1.O2 (O), U3.D0
RESET: JP1.3, RESET0.A, RESET0.A' (P1), U3.RESET (/RESET)
RX: U1.P$10 (RX), U4.12 (5Y)
RX_5V: SW1.P2, U4.11 (5A)
SCK: R9.2, U3.D13, U4.3 (1A), U$9.5
SD_CD: CN2.CD1 (CARD_DETECT), JP6.5
SD_CS: JP6.4, R5.2, U3.D10, U4.7 (3A), U$9.8
SD_CSIN: CN2.2 (CS), U4.6 (3Y)
SD_DATAIN: CN2.3 (DATA_IN), U4.4 (2Y)
SD_SCKIN: CN2.5 (SCLK), U4.2 (1Y)
TX: SW1.P1, U1.P$9 (TX)
VBACKUP: B1.+$1 (+), U1.P$4 (VBACKUP)

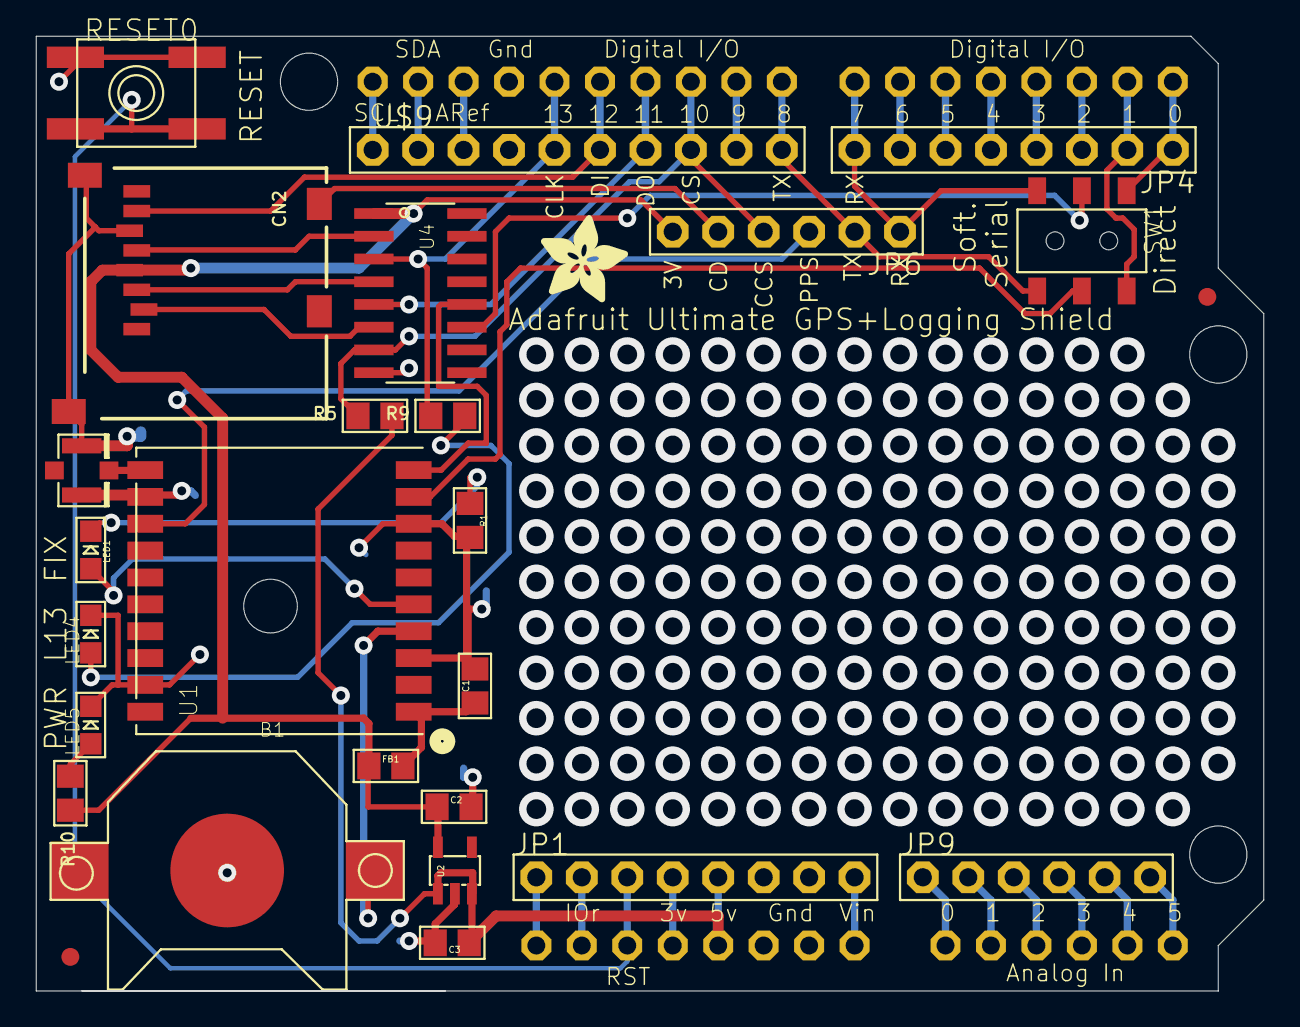
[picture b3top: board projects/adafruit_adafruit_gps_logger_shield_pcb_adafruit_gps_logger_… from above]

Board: 2 copper layers, 68.6 x 53.3 mm, 32 parts (1 on the bottom side), 46 nets.

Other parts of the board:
@HOLE0, @HOLE1, @HOLE2: (no value)
U$13: ADAFRUIT_5MM
U$15: ADAFRUIT_TEXT_30MM
